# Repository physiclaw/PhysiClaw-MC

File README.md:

# PhysiClaw-MC

PCW-MC-01 v1.0 is a 70 × 50 mm, four-layer ESP32 controller for two bipolar
stepper motors and one 12 V / 0.8 A solenoid. Factory acceptance and bench
qualification are pending.

## Repository layout

| Directory | Start here |
| --- | --- |
| `pcb/kicad/` | [Editable KiCad project](pcb/kicad/PCW-MC-01.kicad_pro) with local libraries |
| `docs/` | [Design notes](docs/design.md) |
| `firmware/` | [FluidNC configuration and operation](firmware/README.md) |
| `manufacturing/` | [Fabrication, assembly, and first-article guide](manufacturing/process.md) |
| `tools/`, `tests/` | [Build](#generate-the-manufacturing-files) and [verification](#edit-and-verify-the-design) |

## Generate the manufacturing files

Install [KiCad 10 or newer], [uv], and GNU Make. On Windows, install GNU Make with
`choco install make` if it is missing, then open a new terminal.

The build checks `PATH` and the standard KiCad 10 installation paths on macOS
and Windows. For a different installation, set `KICAD_CLI` to the executable's
full path. On headless Linux, install Xvfb and run `xvfb-run -a make build` to
generate the 3D renders.

```sh
git clone https://github.com/physiclaw/PhysiClaw-MC.git
cd PhysiClaw-MC
make build
```

Each successful build replaces `dist/` (JLC order files) and `build/`
(review files). The review files include `build/schematic.pdf`, the assembly
BOM at `build/assembly/assembly.csv`, the FluidNC configuration in
`build/firmware/config.yaml`, the bare-board STEP model and
`build/manifest.json` with source and output checksums. Use
`make build VERBOSE=1` to show KiCad output.

`uv` uses Python 3.12 and installs dependencies from `uv.lock`.

For offline builds, run `uv sync --locked` once while online, then use
`make UV_OFFLINE=1 build`.

### Review the PCB

Open the [中文互动图解](docs/pcb-guide/index.html) in a browser to explore the
nine circuit areas. Select a component label to compare its routed footprint
with the same part in the KiCad schematic. Each area has a standalone SVG
with signal directions and fitted-part specifications. All 107 references
are covered, and the guide works offline from the checkout. To refresh the
illustrations after a build, run `uv run --locked python tools/guide_illustrations.py`.
The [IC pin atlas](docs/pcb-guide/index.html#ics) has one annotated routing
close-up per fitted IC or module, with pad numbers, signal directions and board connections.

The views are in `build/view/`.

- **Copper.** The `L1-*` through `L4-*` SVGs show filled copper in top-view
  alignment. `L3-power.svg` distinguishes the 12 V, 3.3 V and ground pours.
- **Routing.** `top-routing.svg`, `bottom-routing.svg`, and
  `top-bottom-routing.svg` show traces, pads, and vias with pours hidden.
  `usb-routing.svg` is the D+/D− close-up.
- **Reference.** `component-reference.svg` maps designators to footprints.
  `probe-map.svg` locates test points on both sides.
- **Fabrication.** `drill-and-slot-map.svg` shows holes, slots, and capped vias.
  `mask-and-paste.svg` shows mask and stencil apertures.
- **3D renders.** `3d-assembly.png` shows the populated board in perspective.
  `3d-top.png` and `3d-underside.png` show the two faces directly. Some package
  models use simplified geometry.

## Order a prototype at JLC

Run `make build` from the checkout you intend to order. Use the Gerbers, BOM,
and CPL from that build together.

| JLC upload field | File |
| --- | --- |
| PCB (Gerbers and drills) | `dist/PHYSICLAW-JLC-Gerbers.zip` |
| Proposed assembly panel (拼板示意图) | `dist/PHYSICLAW-JLC-panel.jpg` |
| SMT bill of materials (BOM) | `dist/PHYSICLAW-JLC-BOM.csv` |
| SMT placement file (CPL) | `dist/PHYSICLAW-JLC-CPL-mm.csv` |

Check the outline, drills, mask, and silkscreen in a Gerber viewer, then upload
the ZIP. Select **Standard SMT assembly (标准型)** at JLC China for the top
side. Upload each CSV separately and set placement units to millimetres.

Send JLC the [manufacturing guide](manufacturing/process.md) and both files in
`dist/fabrication/`. Before ordering, confirm the stackup, via fill and cap,
and assembly panel with CAM.

Approve the assembly preview against `build/assembly/top-assembly.pdf` and
`build/assembly/placement-review.csv`. Use `build/assembly/tht-bom.csv` for
through-hole assembly.

## Edit and verify the design

Update the schematic's MPN, LCSC code, datasheet and manufacturer (when
specified), then run **Update PCB from Schematic**. For substitutions, verify the
footprint and update the [JLC part table](manufacturing/jlc-parts.csv).
Run the placement geometry checks and regenerate the outputs. The build also
runs KiCad ERC and DRC.

```sh
make check
make build
```

The [CI workflow](.github/workflows/ci.yml) runs both commands on GitHub's
latest Linux, Windows, and macOS runners with KiCad 10.0.8. It also tests
newer stable releases as their installers and Linux images become available.

## Contributing and releases

See [contribution and release instructions](CONTRIBUTING.md) and the
[changelog](CHANGELOG.md). [OSHWA sharing best practices](https://oshwa.org/resources/sharing-best-practices/)

## License

Copyright © 2026 QiaoQian

The original hardware design and its source files, documentation, firmware
configuration, and tools use the [MIT License](LICENSE). The KiCad libraries
and upstream FluidNC firmware retain their respective licenses.
[KiCad library sources](pcb/kicad/libraries/sources.json) ·
[KiCad library license](pcb/kicad/libraries/KICAD-LICENSE.md)

[KiCad 10 or newer]: https://www.kicad.org/download/
[uv]: https://docs.astral.sh/uv/getting-started/installation/

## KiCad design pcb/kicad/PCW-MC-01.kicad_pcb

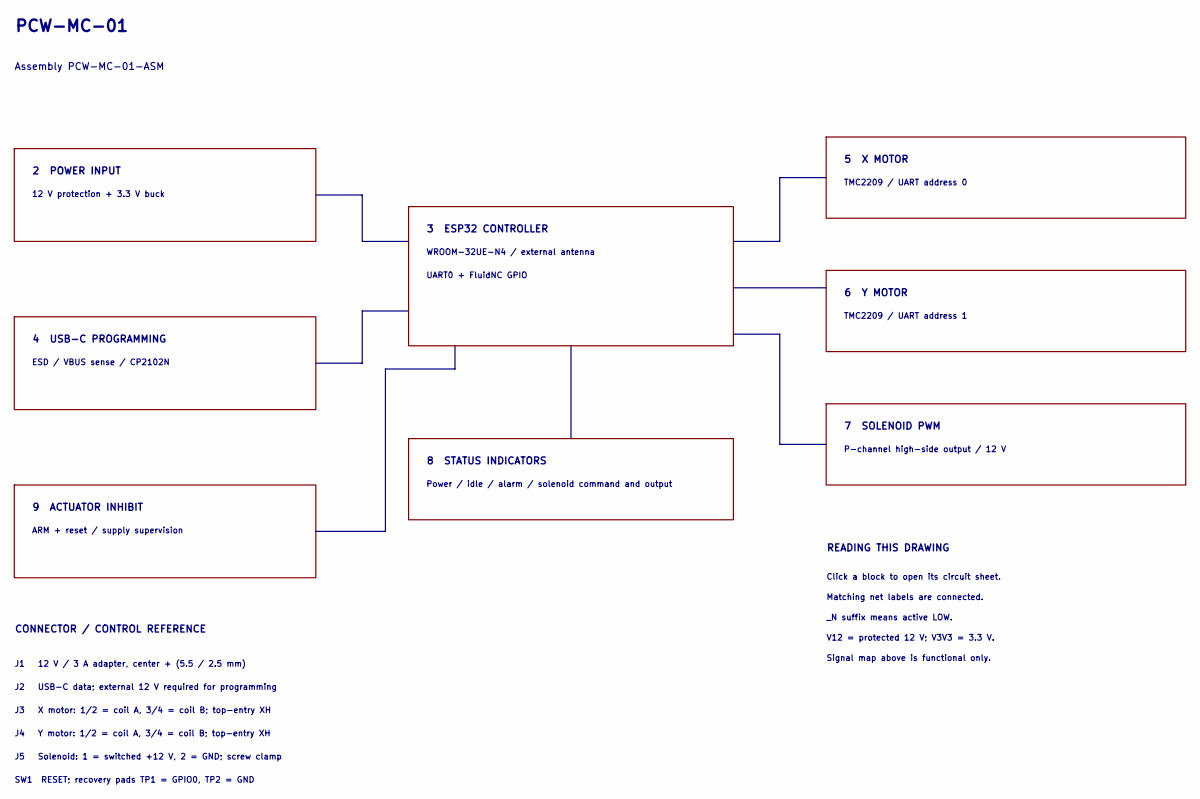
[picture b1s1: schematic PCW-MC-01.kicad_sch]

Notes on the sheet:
PCW-MC-01
Assembly PCW-MC-01-ASM
2 POWER INPUT
12 V protection + 3.3 V buck
3 ESP32 CONTROLLER
WROOM-32UE-N4 / external antenna
UART0 + FluidNC GPIO
4 USB-C PROGRAMMING
ESD / VBUS sense / CP2102N
5 X MOTOR
TMC2209 / UART address 0
6 Y MOTOR
TMC2209 / UART address 1
7 SOLENOID PWM
P-channel high-side output / 12 V
8 STATUS INDICATORS
Power / idle / alarm / solenoid command and output
9 ACTUATOR INHIBIT
ARM + reset / supply supervision
CONNECTOR / CONTROL REFERENCE
J1 12 V / 3 A adapter, center + (5.5 / 2.5 mm)
J2 USB-C data; external 12 V required for programming
J3 X motor: 1/2 = coil A, 3/4 = coil B; top-entry XH
J4 Y motor: 1/2 = coil A, 3/4 = coil B; top-entry XH
J5 Solenoid: 1 = switched +12 V, 2 = GND; screw clamp
SW1 RESET; recovery pads TP1 = GPIO0, TP2 = GND
READING THIS DRAWING
Click a block to open its circuit sheet.
Matching net labels are connected.
_N suffix means active LOW.
V12 = protected 12 V; V3V3 = 3.3 V.
Signal map above is functional only.

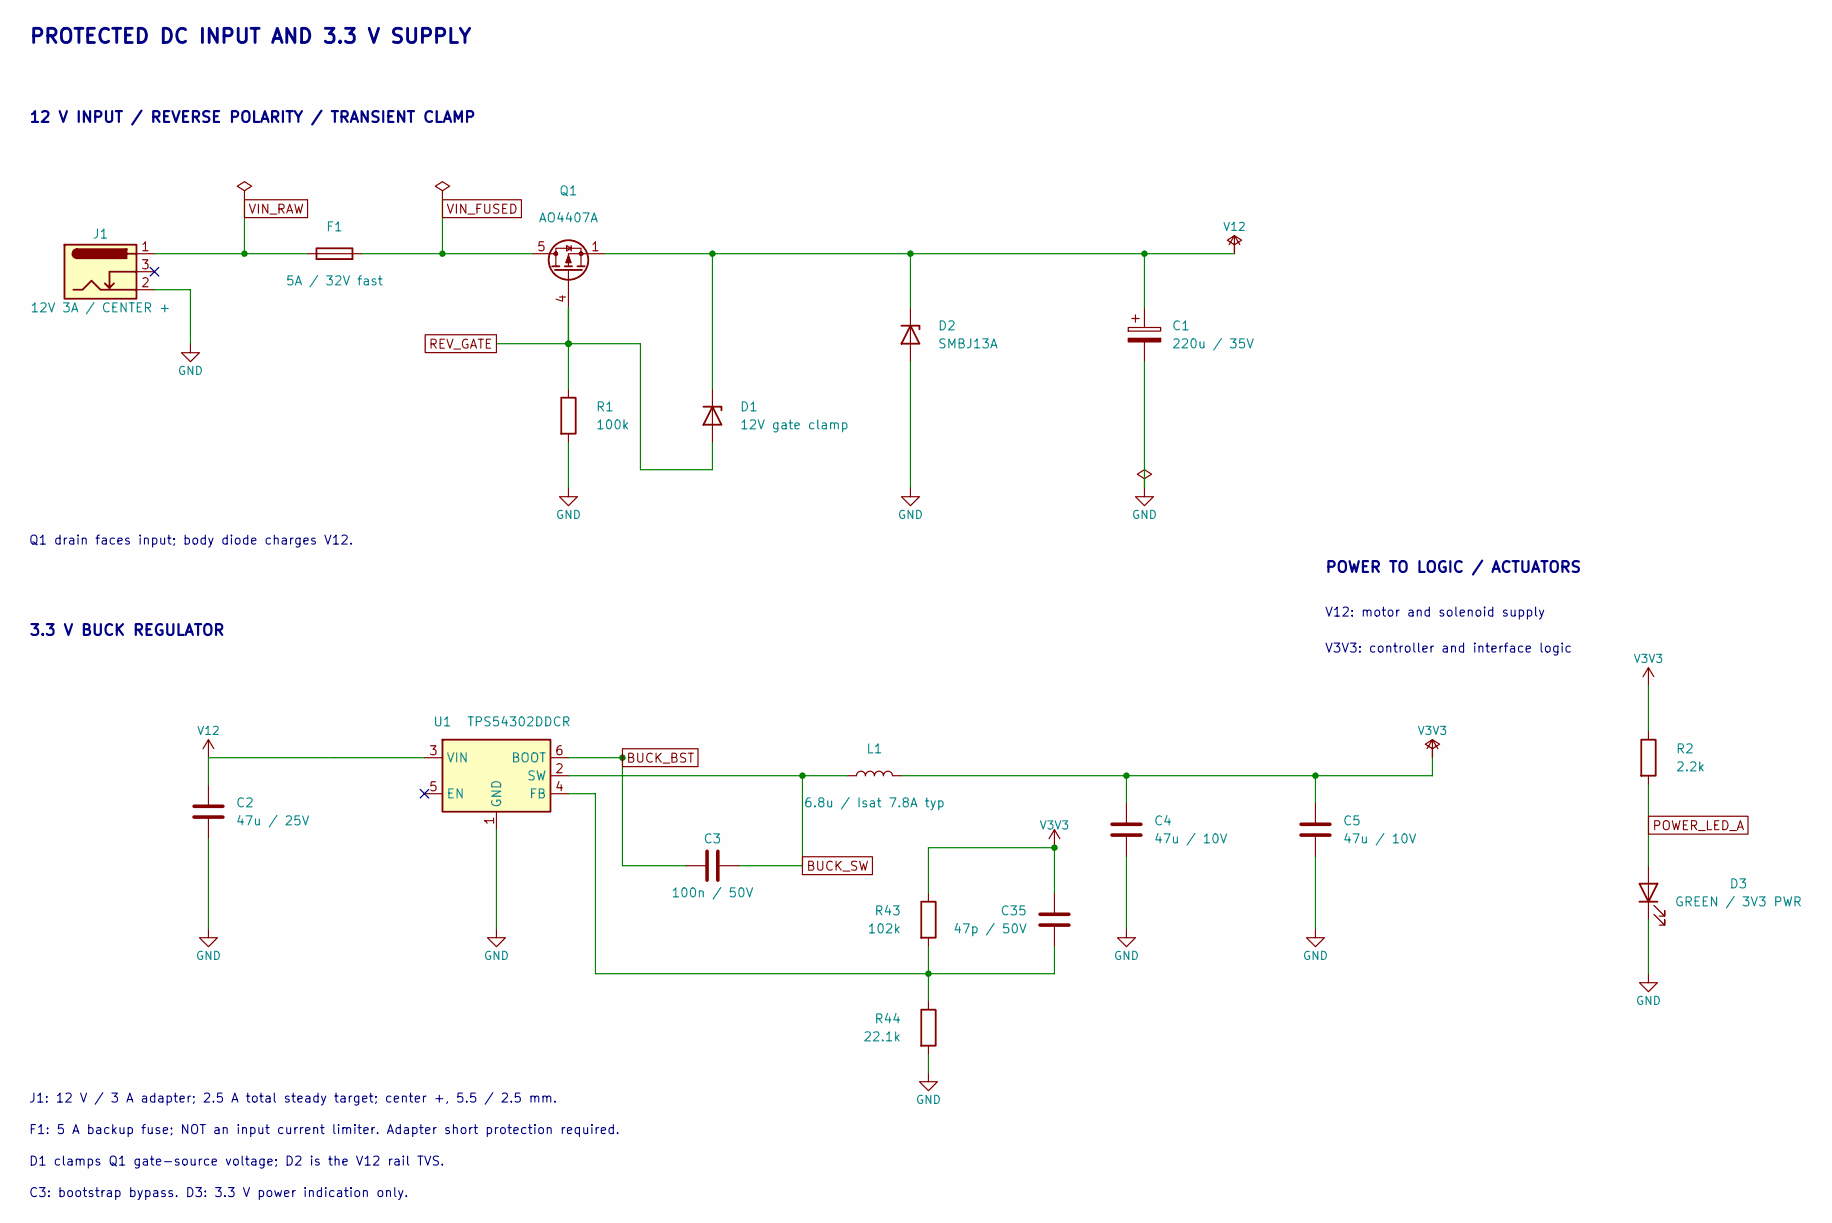
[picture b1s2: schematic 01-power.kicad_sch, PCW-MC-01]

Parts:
C1: 220u / 35V; Capacitor_THT_CP_Radial_D8.0mm_P3.50mm; MPN UHV1V221MPD1TD; LCSC C5111097
C2: 47u / 25V; Capacitor_SMD_C_1210_3225Metric; MPN MSAST32MAB5476MPNDT1; LCSC C6231537
C3: 100n / 50V; Capacitor_SMD_C_0603_1608Metric; MPN CL10B104KB8NNNC; LCSC C1591
C4, C5: 47u / 10V; Capacitor_SMD_C_0805_2012Metric; MPN GRM21BR61A476ME15L; LCSC C124129
C35: 47p / 50V; Capacitor_SMD_C_0603_1608Metric; MPN CL10C470JB8NNNC; LCSC C1671
D1: 12V gate clamp; Diode_SMD_D_SOD-123; MPN BZT52C12; LCSC C173429
D2: SMBJ13A; Diode_SMD_D_SMB; MPN SMBJ13A; LCSC C151252
D3: GREEN / 3V3 PWR; LED_SMD_LED_0603_1608Metric; MPN LTST-C190KGKT; LCSC C125094
F1: 5A / 32V fast; Fuse_Fuse_0603_1608Metric; MPN 0467005.NRHF; LCSC C151140
J1: 12V 3A / CENTER +; Connector_BarrelJack_BarrelJack_CUI_PJ-102BH_Horizontal; MPN PJ-102BH; LCSC C3095964
L1: 6.8u / Isat 7.8A typ; Bourns_SRP5050FA; MPN FEXL0550A-6R8M; LCSC C5378515
Q1: AO4407A; Package_SO_SOIC-8_3.9x4.9mm_P1.27mm; MPN AO4407A; LCSC C2841482
R1: 100k; Resistor_SMD_R_0603_1608Metric; MPN 0603WAF1003T5E; LCSC C25803
R2: 2.2k; Resistor_SMD_R_0603_1608Metric; MPN 0603WAF2201T5E; LCSC C4190
R43: 102k; Resistor_SMD_R_0603_1608Metric; MPN RT0603BRD07102KL; LCSC C861068
R44: 22.1k; Resistor_SMD_R_0603_1608Metric; MPN RT0603BRD0722K1L; LCSC C723484
U1: TPS54302DDCR; Texas_DDC0006A; MPN TPS54302DDCR; LCSC C311983

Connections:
BUCK_BST: C3.1, U1.6 (BOOT)
BUCK_SW: C3.2, L1.1, U1.2 (SW)
GND: C1.2, C2.2, C4.2, C5.2, D2.2 (A), D3.1 (K), J1.2, R1.2, R44.2, U1.1 (GND); also elsewhere on the board
unnamed: C35.2, R43.2, R44.1, U1.4 (FB)
POWER_LED_A: D3.2 (A), R2.2
REV_GATE: D1.2 (A), Q1.4 (G), R1.1
V3V3: C4.1, C5.1, C35.1, L1.2, R2.1, R43.1; also elsewhere on the board
V12: C1.1, C2.1, D1.1 (K), D2.1 (K), Q1.1 (S), Q1.2 (S), Q1.3 (S), U1.3 (VIN); also elsewhere on the board
VIN_FUSED: F1.2, Q1.5 (D), Q1.6 (D), Q1.7 (D), Q1.8 (D)
VIN_RAW: F1.1, J1.1

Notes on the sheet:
PROTECTED DC INPUT AND 3.3 V SUPPLY
12 V INPUT / REVERSE POLARITY / TRANSIENT CLAMP
Q1 drain faces input; body diode charges V12.
3.3 V BUCK REGULATOR
J1: 12 V / 3 A adapter; 2.5 A total steady target; center +, 5.5 / 2.5 mm.
F1: 5 A backup fuse; NOT an input current limiter. Adapter short protection required.
D1 clamps Q1 gate-source voltage; D2 is the V12 rail TVS.
C3: bootstrap bypass. D3: 3.3 V power indication only.
POWER TO LOGIC / ACTUATORS
V12: motor and solenoid supply
V3V3: controller and interface logic

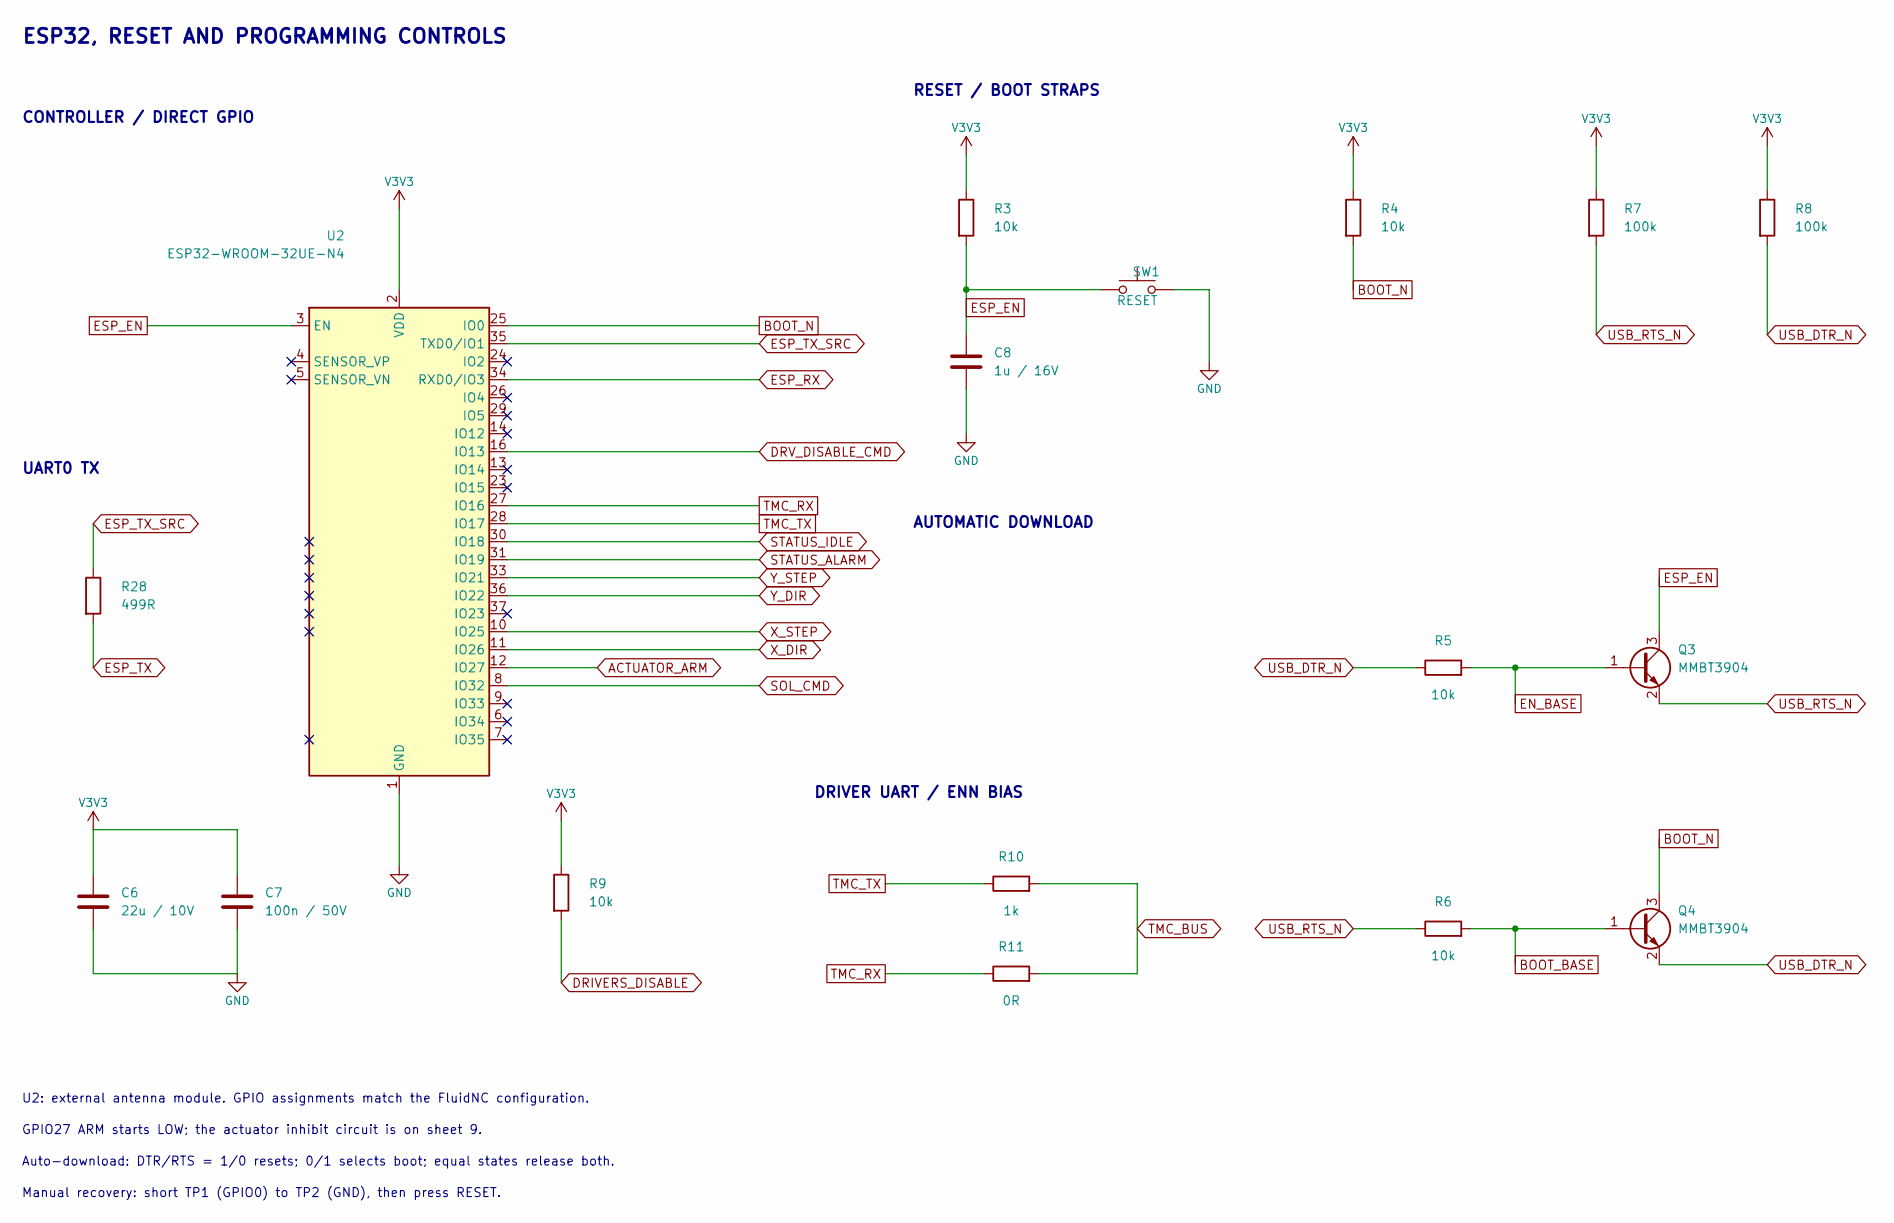
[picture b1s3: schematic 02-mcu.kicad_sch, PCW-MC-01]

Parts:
C6: 22u / 10V; Capacitor_SMD_C_0805_2012Metric; MPN GRM21BR61A226ME44L; LCSC C441864
C7: 100n / 50V; Capacitor_SMD_C_0603_1608Metric; MPN CL10B104KB8NNNC; LCSC C1591
C8: 1u / 16V; Capacitor_SMD_C_0603_1608Metric; MPN CL10A105KO8NNNC; LCSC C1592
Q3, Q4: MMBT3904; Package_TO_SOT_SMD_SOT-23; MPN MMBT3904; LCSC C20526
R3, R4, R5, R6, R9: 10k; Resistor_SMD_R_0603_1608Metric; MPN 0603WAF1002T5E; LCSC C25804
R7, R8: 100k; Resistor_SMD_R_0603_1608Metric; MPN 0603WAF1003T5E; LCSC C25803
R10: 1k; Resistor_SMD_R_0603_1608Metric; MPN 0603WAF1001T5E; LCSC C21190
R11: 0R; Resistor_SMD_R_0603_1608Metric; MPN 0603WAF0000T5E; LCSC C21189
R28: 499R; Resistor_SMD_R_0402_1005Metric; MPN 0402WGF4990TCE; LCSC C4125
SW1: RESET; Button_Switch_SMD_SW_SPST_TS1187A; MPN TS-1187A-B-A-B; LCSC C318884
U2: ESP32-WROOM-32UE-N4; RF_Module_ESP32-WROOM-32UE; MPN ESP32-WROOM-32UE-N4; LCSC C701344

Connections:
ACTUATOR_ARM: U2.12 (IO27); also elsewhere on the board
BOOT_BASE: Q4.1 (B), R6.2
BOOT_N: Q4.3 (C), R4.2, U2.25 (IO0); also elsewhere on the board
DRIVERS_DISABLE: R9.2; also elsewhere on the board
DRV_DISABLE_CMD: U2.16 (IO13); also elsewhere on the board
EN_BASE: Q3.1 (B), R5.2
ESP_EN: C8.1, Q3.3 (C), R3.2, SW1.1, U2.3 (EN); also elsewhere on the board
ESP_RX: U2.34 (RXD0/IO3); also elsewhere on the board
ESP_TX: R28.2; also elsewhere on the board
ESP_TX_SRC: R28.1, U2.35 (TXD0/IO1)
GND: C6.2, C7.2, C8.2, SW1.2, U2.1 (GND), U2.15 (GND), U2.38 (GND), U2.39 (GND); also elsewhere on the board
SOL_CMD: U2.8 (IO32); also elsewhere on the board
STATUS_ALARM: U2.31 (IO19); also elsewhere on the board
STATUS_IDLE: U2.30 (IO18); also elsewhere on the board
TMC_BUS: R10.2, R11.2; also elsewhere on the board
TMC_RX: R11.1, U2.27 (IO16)
TMC_TX: R10.1, U2.28 (IO17)
USB_DTR_N: Q4.2 (E), R5.1, R8.2; also elsewhere on the board
USB_RTS_N: Q3.2 (E), R6.1, R7.2; also elsewhere on the board
V3V3: C6.1, C7.1, R3.1, R4.1, R7.1, R8.1, R9.1, U2.2 (VDD); also elsewhere on the board
X_DIR: U2.11 (IO26); also elsewhere on the board
X_STEP: U2.10 (IO25); also elsewhere on the board
Y_DIR: U2.36 (IO22); also elsewhere on the board
Y_STEP: U2.33 (IO21); also elsewhere on the board

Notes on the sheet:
ESP32, RESET AND PROGRAMMING CONTROLS
CONTROLLER / DIRECT GPIO
RESET / BOOT STRAPS
AUTOMATIC DOWNLOAD
DRIVER UART / ENN BIAS
U2: external antenna module. GPIO assignments match the FluidNC configuration.
GPIO27 ARM starts LOW; the actuator inhibit circuit is on sheet 9.
Auto-download: DTR/RTS = 1/0 resets; 0/1 selects boot; equal states release both.
Manual recovery: short TP1 (GPIO0) to TP2 (GND), then press RESET.
UART0 TX

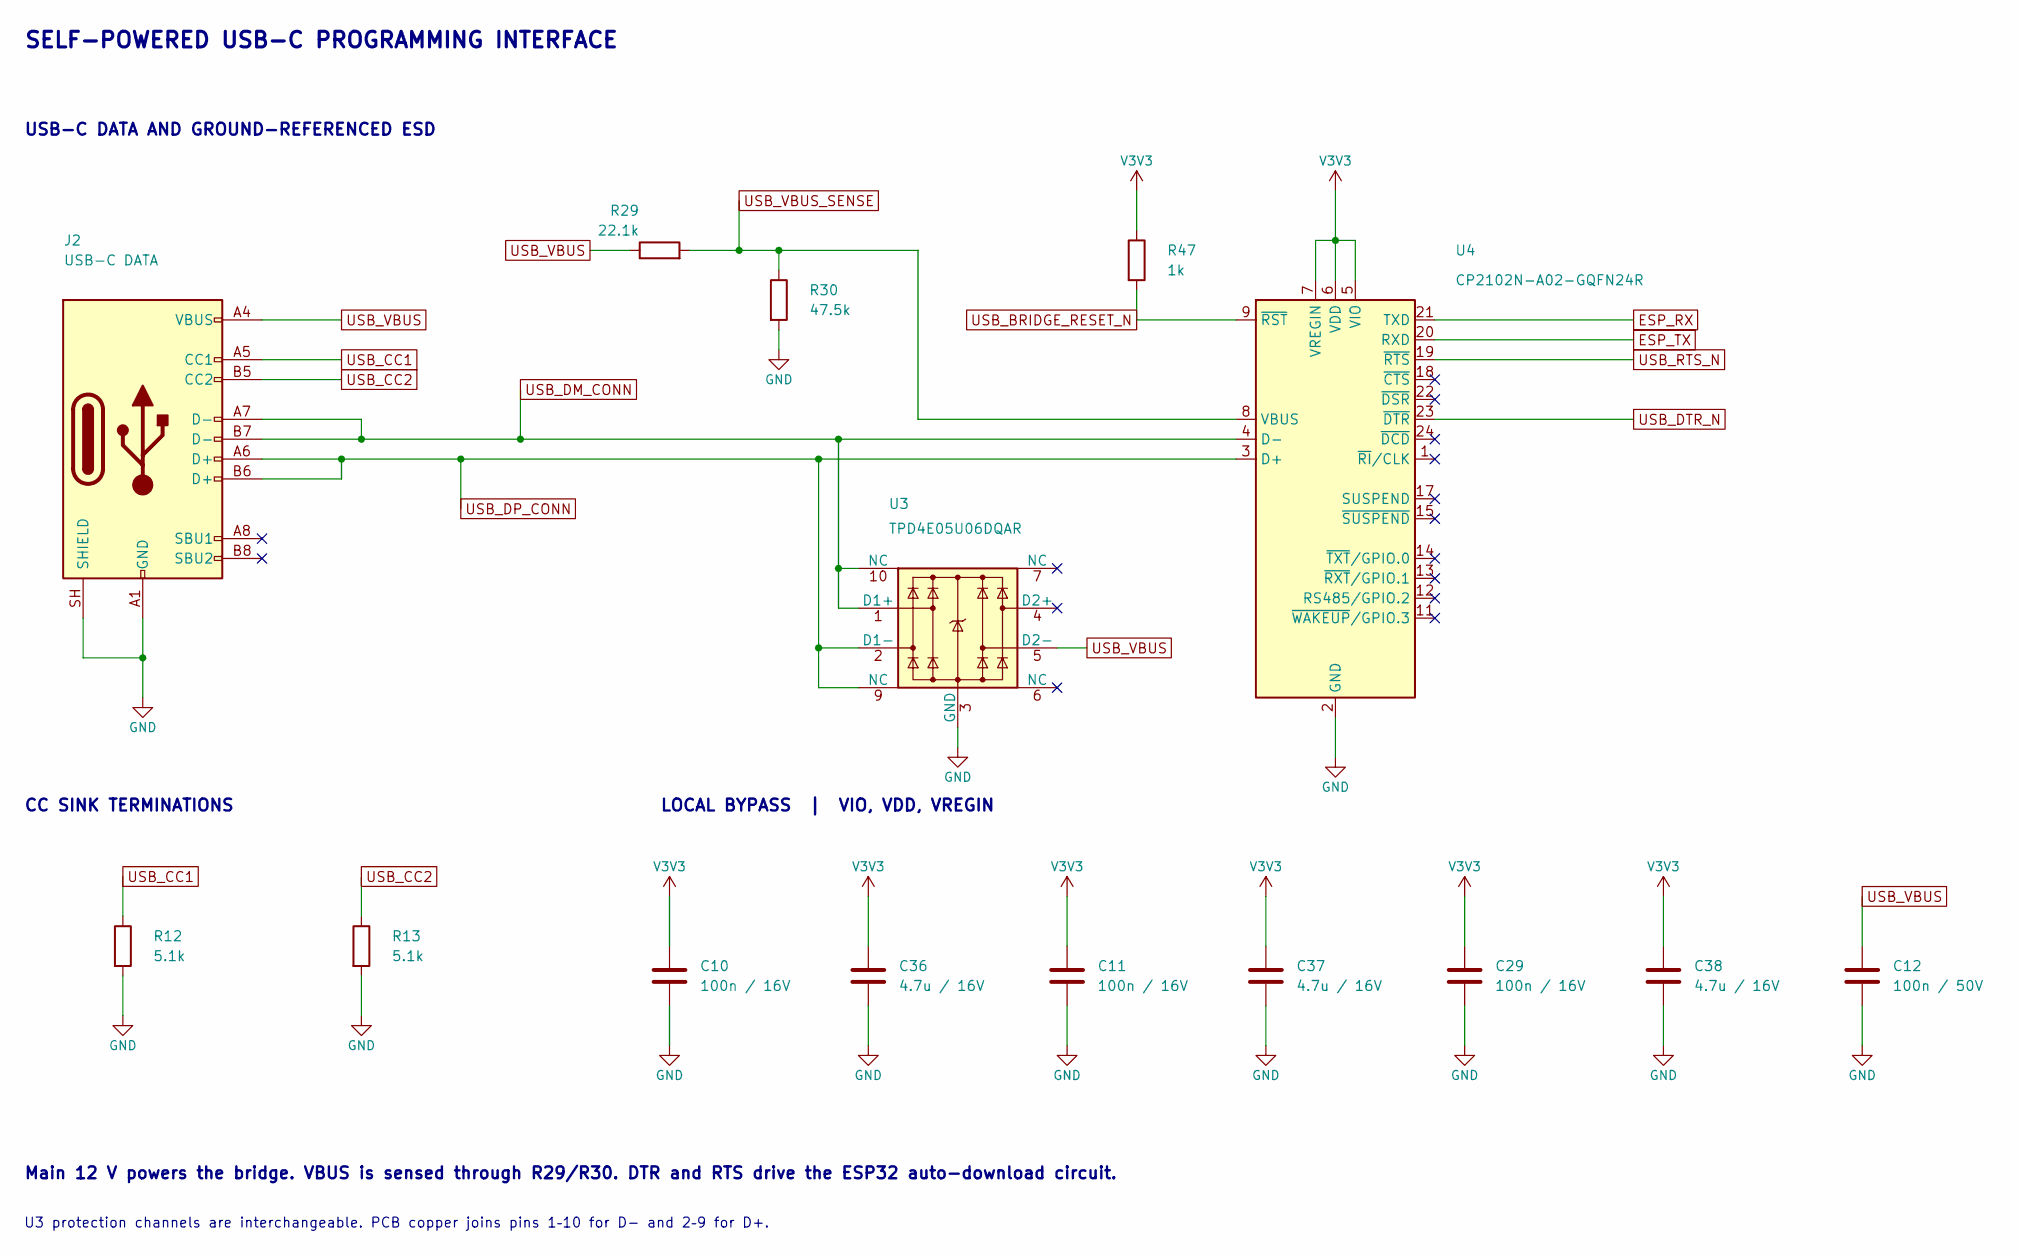
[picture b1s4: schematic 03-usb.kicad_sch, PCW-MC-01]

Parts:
C10, C11, C29: 100n / 16V; Capacitor_SMD_C_0402_1005Metric; MPN CL05B104KO5NNNC; LCSC C1525
C12: 100n / 50V; Capacitor_SMD_C_0603_1608Metric; MPN CL10B104KB8NNNC; LCSC C1591
C36, C37, C38: 4.7u / 16V; Capacitor_SMD_C_0603_1608Metric; MPN CL10A475KO8NNNC; LCSC C19666
J2: USB-C DATA; Connector_USB_USB_C_Receptacle_HRO_TYPE-C-31-M-12; MPN TYPE-C-31-M-12; LCSC C165948
R12, R13: 5.1k; Resistor_SMD_R_0603_1608Metric; MPN 0603WAF5101T5E; LCSC C23186
R29: 22.1k; Resistor_SMD_R_0603_1608Metric; MPN 0603WAF2212T5E; LCSC C25961
R30: 47.5k; Resistor_SMD_R_0603_1608Metric; MPN 0603WAF4752T5E; LCSC C23061
R47: 1k; Resistor_SMD_R_0402_1005Metric; MPN 0402WGF1001TCE; LCSC C11702
U3: TPD4E05U06DQAR; Texas_DQA0010_USON-10; MPN TPD4E05U06DQAR; LCSC C138714
U4: CP2102N-A02-GQFN24R; SiliconLabs_CP2102N_QFN24; MPN CP2102N-A02-GQFN24R; LCSC C969151

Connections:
ESP_RX: U4.21 (TXD); also elsewhere on the board
ESP_TX: U4.20 (RXD); also elsewhere on the board
GND: C10.2, C11.2, C12.2, C29.2, C36.2, C37.2, C38.2, J2.A1 (GND), J2.A12 (GND), J2.B1 (GND), J2.B12 (GND), J2.SH (SHIELD), R12.2, R13.2, R30.2, U3.3 (GND), U3.8 (GND), U4.2 (GND), U4.25 (GND); also elsewhere on the board
USB_BRIDGE_RESET_N: R47.2, U4.9 (~RST)
USB_CC1: J2.A5 (CC1), R12.1
USB_CC2: J2.B5 (CC2), R13.1
USB_DM_CONN: J2.A7 (D-), J2.B7 (D-), U3.1 (D1+), U3.10 (NC), U4.4 (D-)
USB_DP_CONN: J2.A6 (D+), J2.B6 (D+), U3.2 (D1-), U3.9 (NC), U4.3 (D+)
USB_DTR_N: U4.23 (~DTR); also elsewhere on the board
USB_RTS_N: U4.19 (~RTS); also elsewhere on the board
USB_VBUS: C12.1, J2.A4 (VBUS), J2.A9 (VBUS), J2.B4 (VBUS), J2.B9 (VBUS), R29.1, U3.5 (D2-)
USB_VBUS_SENSE: R29.2, R30.1, U4.8 (VBUS)
V3V3: C10.1, C11.1, C29.1, C36.1, C37.1, C38.1, R47.1, U4.5 (VIO), U4.6 (VDD), U4.7 (VREGIN); also elsewhere on the board

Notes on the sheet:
SELF-POWERED USB-C PROGRAMMING INTERFACE
USB-C DATA AND GROUND-REFERENCED ESD
CC SINK TERMINATIONS
LOCAL BYPASS | VIO, VDD, VREGIN
U3 protection channels are interchangeable. PCB copper joins pins 1–10 for D− and 2–9 for D+.
Main 12 V powers the bridge. VBUS is sensed through R29/R30. DTR and RTS drive the ESP32 auto-download circuit.

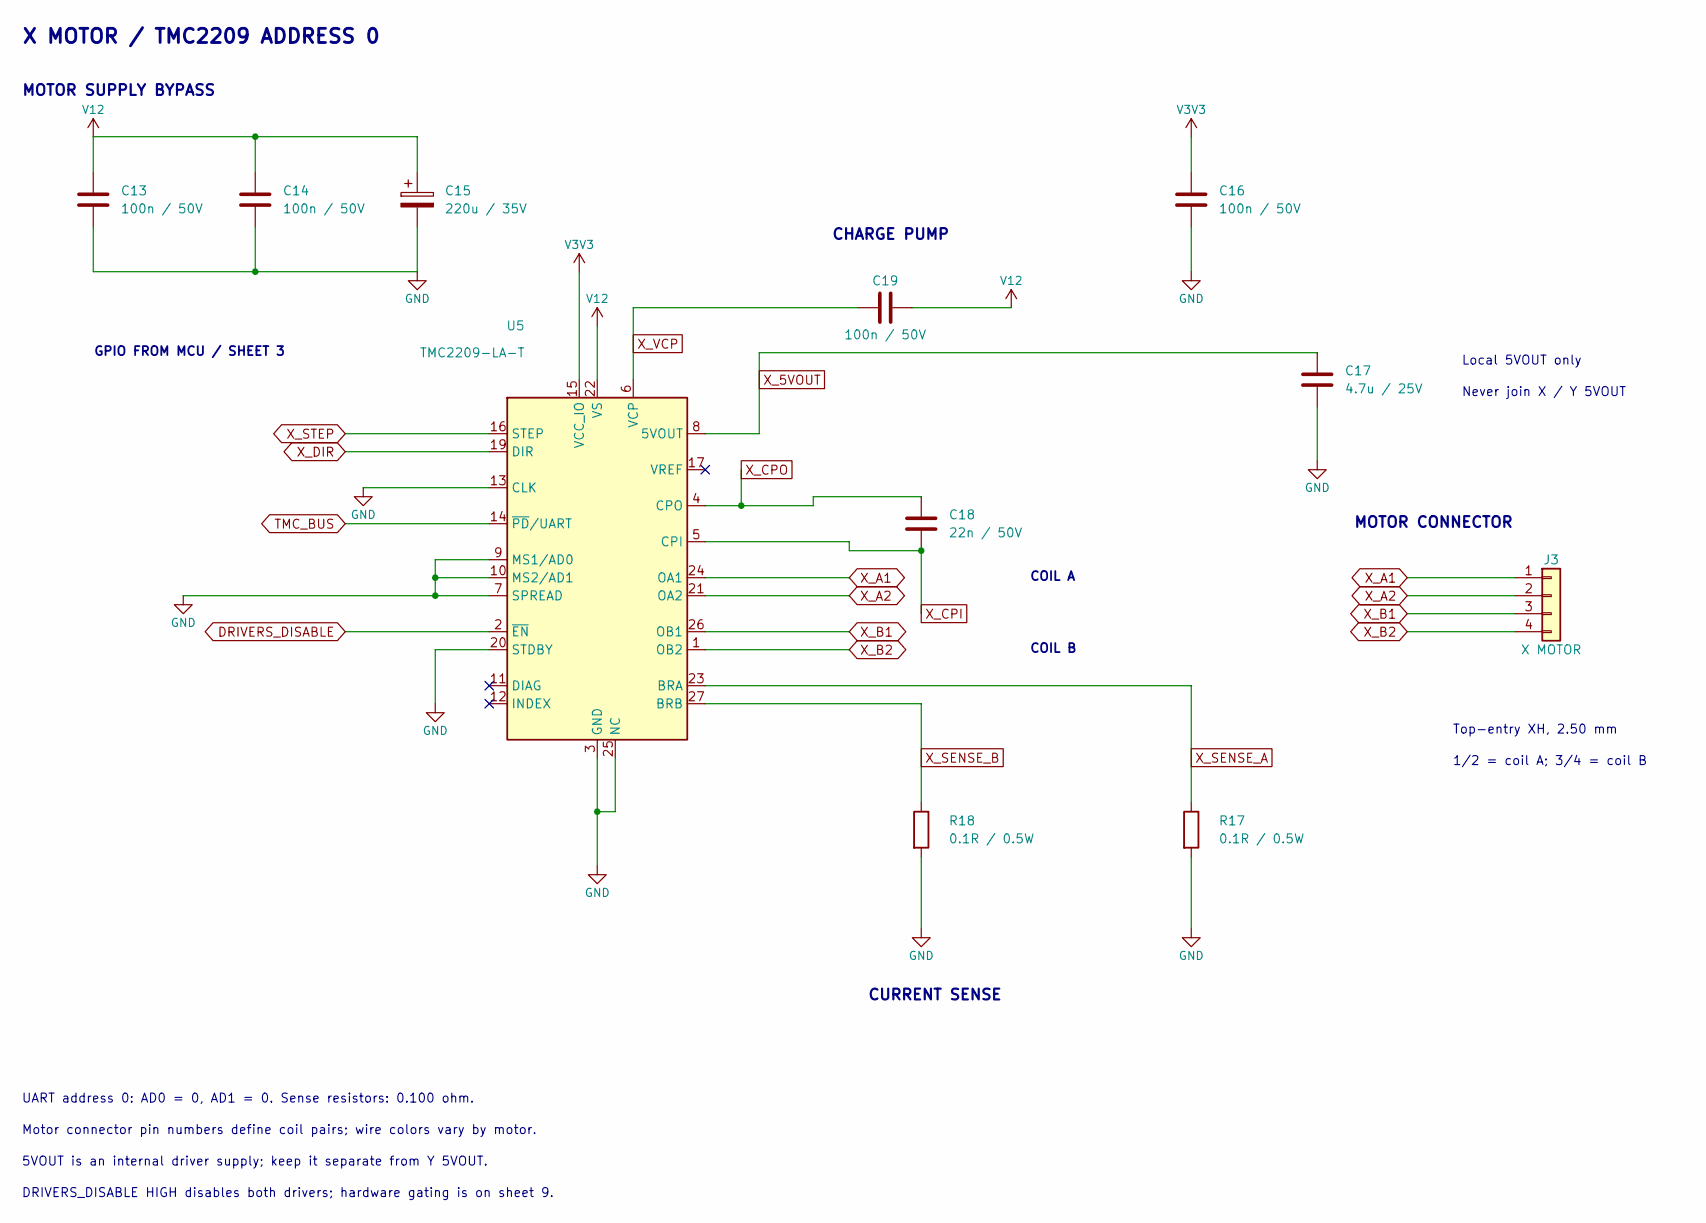
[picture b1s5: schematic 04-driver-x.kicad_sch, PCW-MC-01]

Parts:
C13, C14, C16, C19: 100n / 50V; Capacitor_SMD_C_0603_1608Metric; MPN CL10B104KB8NNNC; LCSC C1591
C15: 220u / 35V; Capacitor_THT_CP_Radial_D8.0mm_P3.50mm; MPN UHV1V221MPD1TD; LCSC C5111097
C17: 4.7u / 25V; Capacitor_SMD_C_0805_2012Metric; MPN CL21B475KAFNNNE; LCSC C98195
C18: 22n / 50V; Capacitor_SMD_C_0603_1608Metric; MPN CL10B223KB8NNNC; LCSC C21122
J3: X MOTOR; Connector_JST_JST_XH_B4B-XH-A_1x04_P2.50mm_Vertical; MPN B4B-XH-A(LF)(SN); LCSC C144395
R17, R18: 0.1R / 0.5W; Resistor_SMD_R_1206_3216Metric; MPN RL1206FR-7W0R1L; LCSC C859927
U5: TMC2209-LA-T; Package_DFN_QFN_VQFN-28-1EP_5x5mm_P0.5mm_EP3.7x3.7mm_Therma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; MPN TMC2209-LA-T; LCSC C2150710

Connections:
DRIVERS_DISABLE: U5.2 (~EN); also elsewhere on the board
GND: C13.2, C14.2, C15.2, C16.2, C17.2, R17.2, R18.2, U5.3 (GND), U5.7 (SPREAD), U5.9 (MS1/AD0), U5.10 (MS2/AD1), U5.13 (CLK), U5.18 (GND), U5.20 (STDBY), U5.25 (NC), U5.29 (GND); also elsewhere on the board
TMC_BUS: U5.14 (~PD/UART); also elsewhere on the board
V3V3: C16.1, U5.15 (VCC_IO); also elsewhere on the board
V12: C13.1, C14.1, C15.1, C19.2, U5.22 (VS), U5.28 (VS); also elsewhere on the board
X_5VOUT: C17.1, U5.8 (5VOUT)
X_A1: J3.1, U5.24 (OA1)
X_A2: J3.2, U5.21 (OA2)
X_B1: J3.3, U5.26 (OB1)
X_B2: J3.4, U5.1 (OB2)
X_CPI: C18.2, U5.5 (CPI)
X_CPO: C18.1, U5.4 (CPO)
X_DIR: U5.19 (DIR); also elsewhere on the board
X_SENSE_A: R17.1, U5.23 (BRA)
X_SENSE_B: R18.1, U5.27 (BRB)
X_STEP: U5.16 (STEP); also elsewhere on the board
X_VCP: C19.1, U5.6 (VCP)

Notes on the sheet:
X MOTOR / TMC2209 ADDRESS 0
MOTOR SUPPLY BYPASS
Local 5VOUT only
Never join X / Y 5VOUT
Top-entry XH, 2.50 mm
1/2 = coil A; 3/4 = coil B
UART address 0: AD0 = 0, AD1 = 0. Sense resistors: 0.100 ohm.
Motor connector pin numbers define coil pairs; wire colors vary by motor.
5VOUT is an internal driver supply; keep it separate from Y 5VOUT.
DRIVERS_DISABLE HIGH disables both drivers; hardware gating is on sheet 9.
COIL A
COIL B
MOTOR CONNECTOR
CHARGE PUMP
CURRENT SENSE
GPIO FROM MCU / SHEET 3

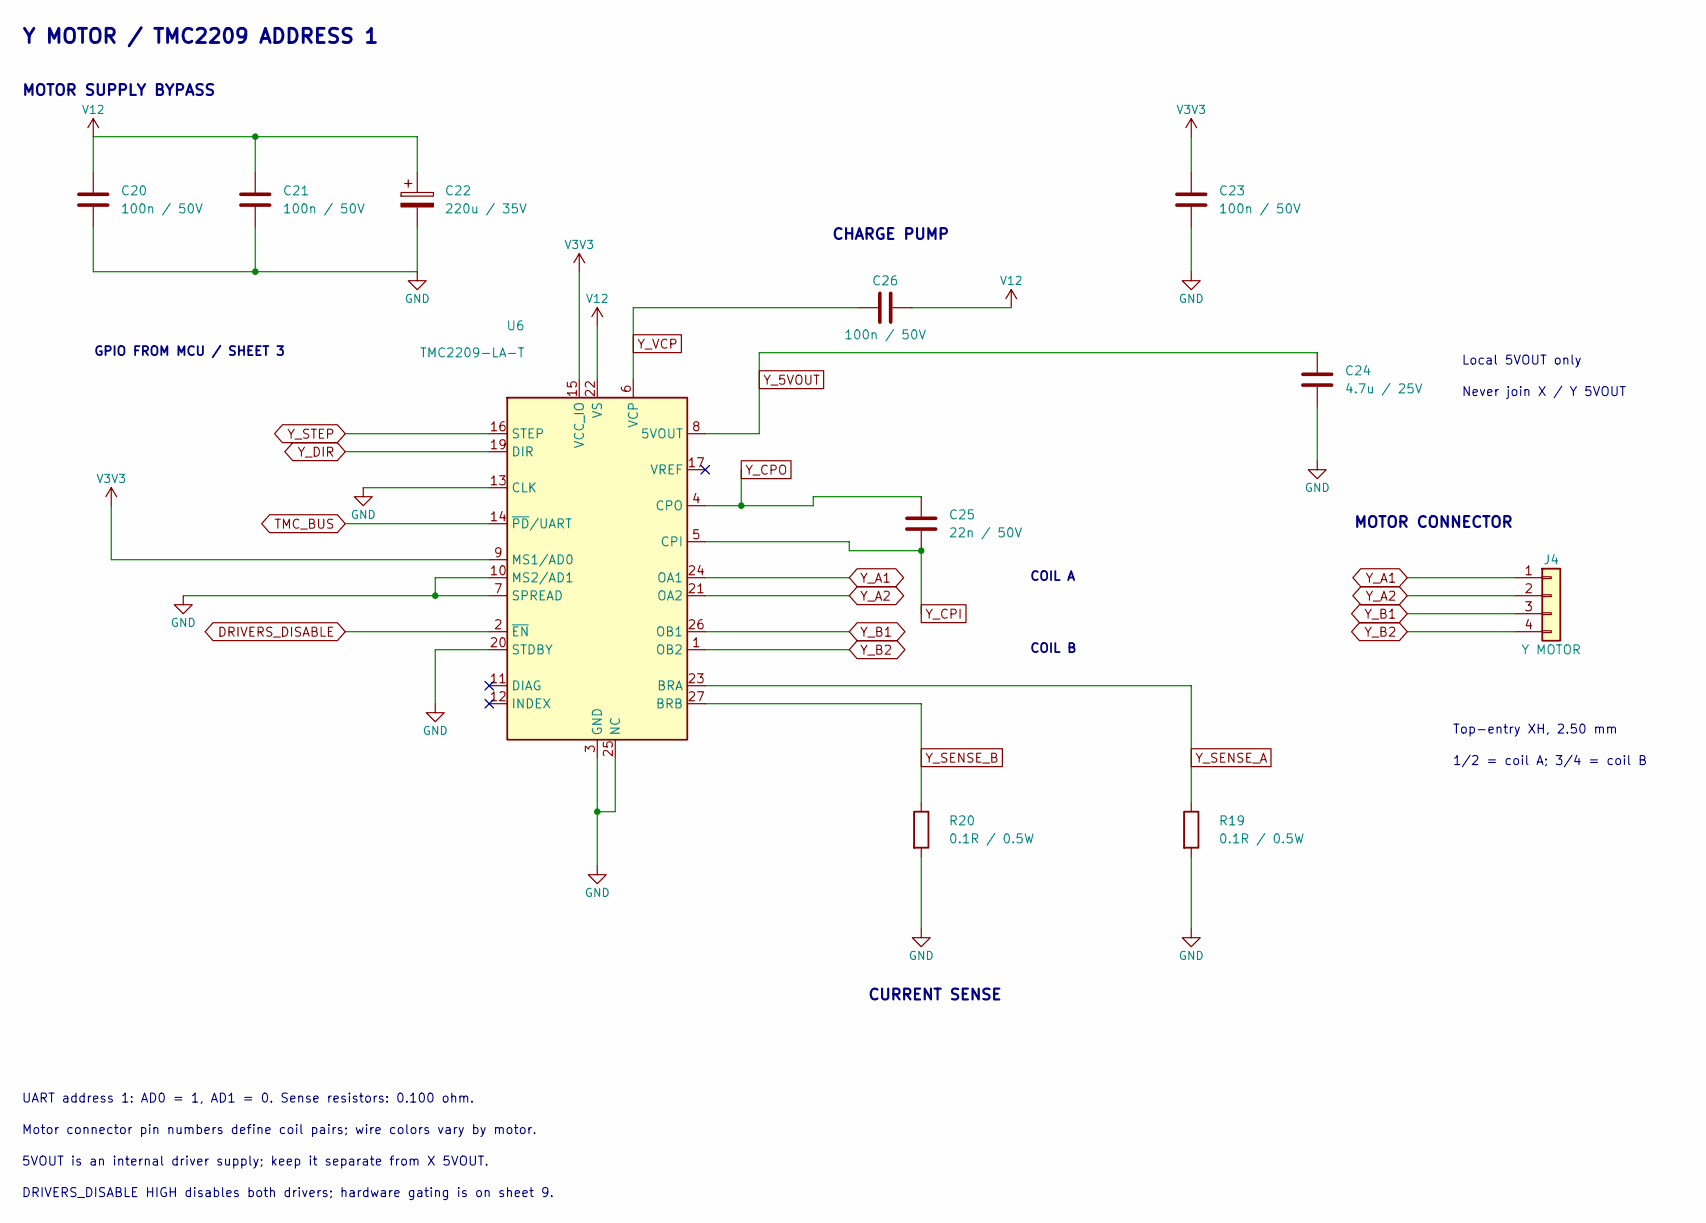
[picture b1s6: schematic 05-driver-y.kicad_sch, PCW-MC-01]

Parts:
C20, C21, C23, C26: 100n / 50V; Capacitor_SMD_C_0603_1608Metric; MPN CL10B104KB8NNNC; LCSC C1591
C22: 220u / 35V; Capacitor_THT_CP_Radial_D8.0mm_P3.50mm; MPN UHV1V221MPD1TD; LCSC C5111097
C24: 4.7u / 25V; Capacitor_SMD_C_0805_2012Metric; MPN CL21B475KAFNNNE; LCSC C98195
C25: 22n / 50V; Capacitor_SMD_C_0603_1608Metric; MPN CL10B223KB8NNNC; LCSC C21122
J4: Y MOTOR; Connector_JST_JST_XH_B4B-XH-A_1x04_P2.50mm_Vertical; MPN B4B-XH-A(LF)(SN); LCSC C144395
R19, R20: 0.1R / 0.5W; Resistor_SMD_R_1206_3216Metric; MPN RL1206FR-7W0R1L; LCSC C859927
U6: TMC2209-LA-T; Package_DFN_QFN_VQFN-28-1EP_5x5mm_P0.5mm_EP3.7x3.7mm_Therma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; MPN TMC2209-LA-T; LCSC C2150710

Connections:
DRIVERS_DISABLE: U6.2 (~EN); also elsewhere on the board
GND: C20.2, C21.2, C22.2, C23.2, C24.2, R19.2, R20.2, U6.3 (GND), U6.7 (SPREAD), U6.10 (MS2/AD1), U6.13 (CLK), U6.18 (GND), U6.20 (STDBY), U6.25 (NC), U6.29 (GND); also elsewhere on the board
TMC_BUS: U6.14 (~PD/UART); also elsewhere on the board
V3V3: C23.1, U6.9 (MS1/AD0), U6.15 (VCC_IO); also elsewhere on the board
V12: C20.1, C21.1, C22.1, C26.2, U6.22 (VS), U6.28 (VS); also elsewhere on the board
Y_5VOUT: C24.1, U6.8 (5VOUT)
Y_A1: J4.1, U6.24 (OA1)
Y_A2: J4.2, U6.21 (OA2)
Y_B1: J4.3, U6.26 (OB1)
Y_B2: J4.4, U6.1 (OB2)
Y_CPI: C25.2, U6.5 (CPI)
Y_CPO: C25.1, U6.4 (CPO)
Y_DIR: U6.19 (DIR); also elsewhere on the board
Y_SENSE_A: R19.1, U6.23 (BRA)
Y_SENSE_B: R20.1, U6.27 (BRB)
Y_STEP: U6.16 (STEP); also elsewhere on the board
Y_VCP: C26.1, U6.6 (VCP)

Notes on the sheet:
Y MOTOR / TMC2209 ADDRESS 1
MOTOR SUPPLY BYPASS
Local 5VOUT only
Never join X / Y 5VOUT
Top-entry XH, 2.50 mm
1/2 = coil A; 3/4 = coil B
UART address 1: AD0 = 1, AD1 = 0. Sense resistors: 0.100 ohm.
Motor connector pin numbers define coil pairs; wire colors vary by motor.
5VOUT is an internal driver supply; keep it separate from X 5VOUT.
DRIVERS_DISABLE HIGH disables both drivers; hardware gating is on sheet 9.
COIL A
COIL B
MOTOR CONNECTOR
CHARGE PUMP
CURRENT SENSE
GPIO FROM MCU / SHEET 3
